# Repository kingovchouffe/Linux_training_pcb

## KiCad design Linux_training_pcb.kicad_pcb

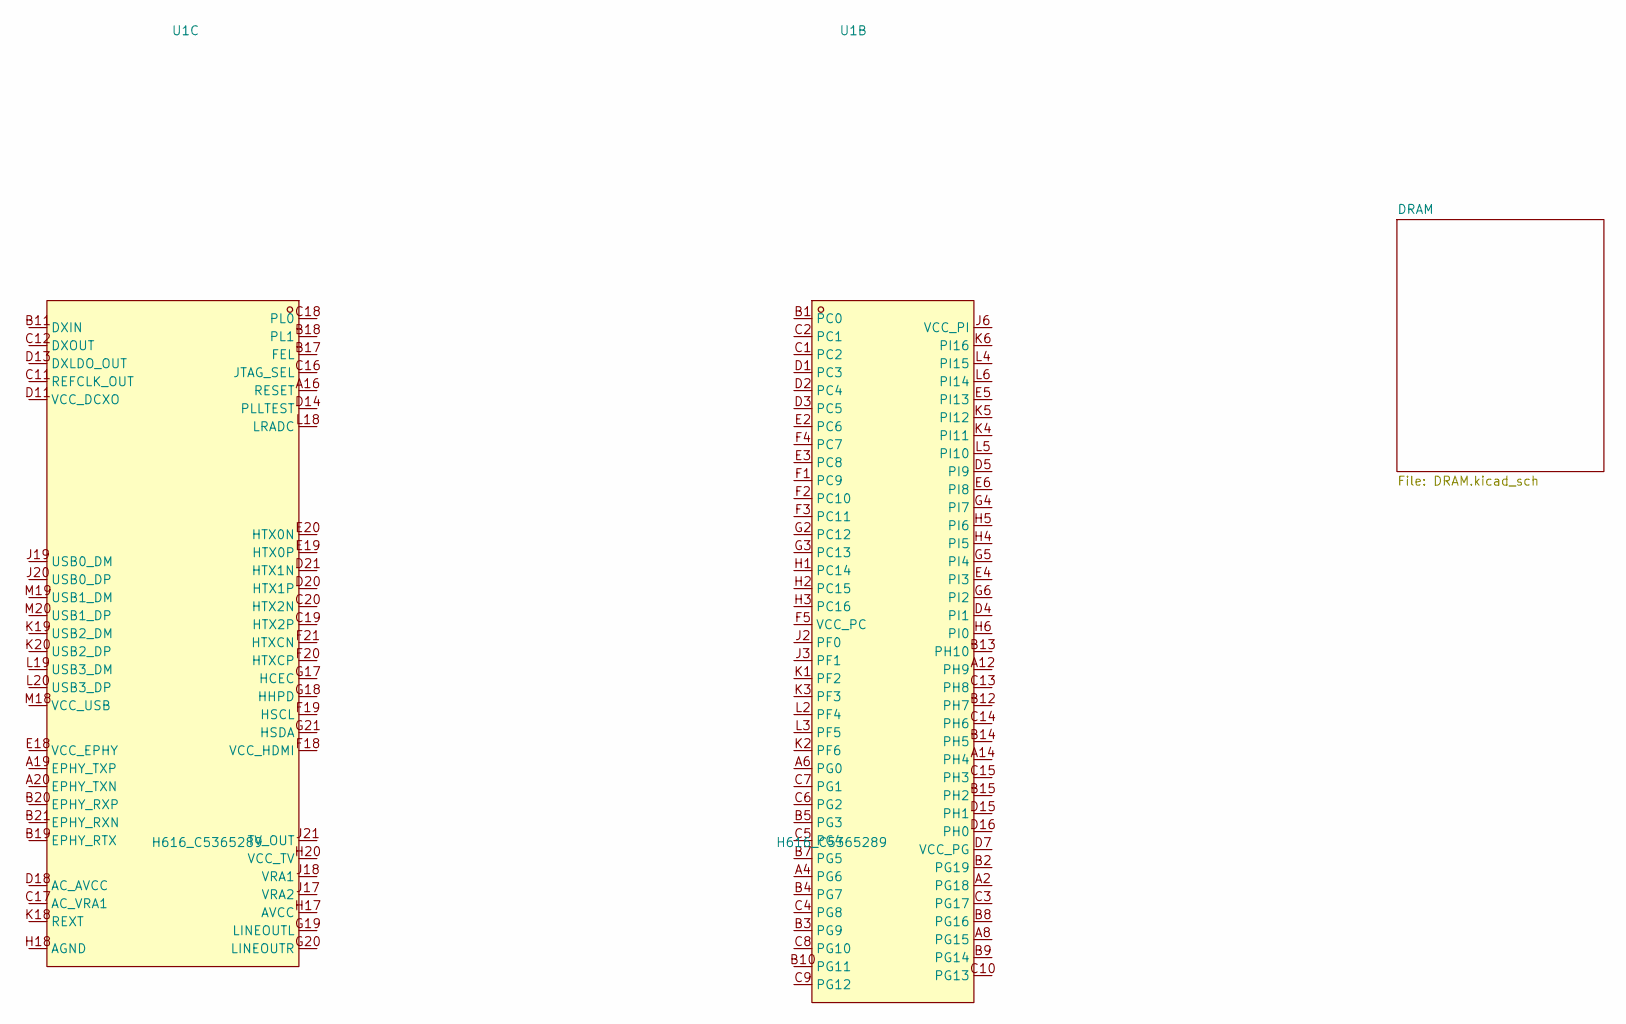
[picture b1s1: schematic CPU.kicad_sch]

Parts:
U1: H616_C5365289; BGA-284_L14.0-W12.0-P0.65-TL; MPN H616; LCSC Part C5365289

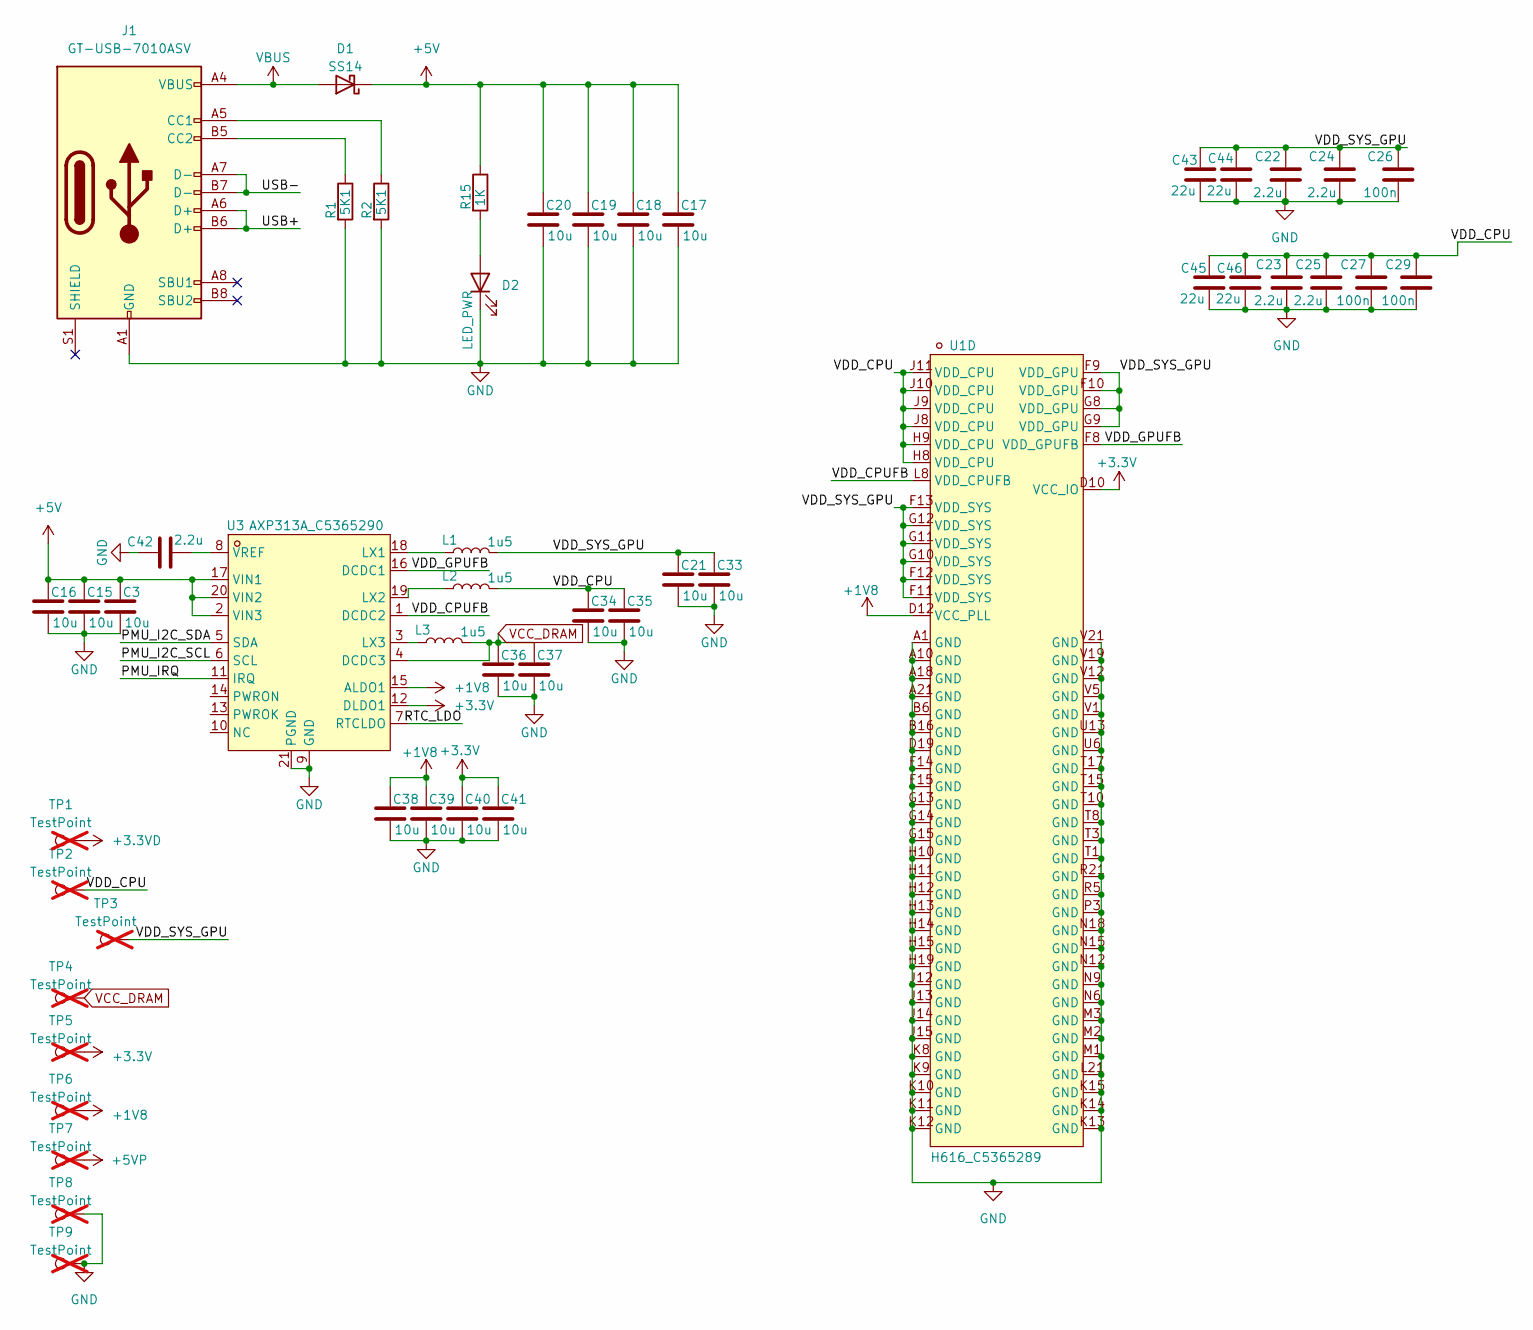
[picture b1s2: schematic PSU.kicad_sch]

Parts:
C3, C15, C16, C17, C18, C19, C20, C21, C33, C34, C35, C36, C37, C38, C39, C40, C41: 10u; C_0603_1608Metric
C22, C23, C24, C25, C42: 2.2u; C_0402_1005Metric; Part Number CL05A225KO5NQNC
C26, C27, C29: 100n; C_0402_1005Metric; Part Number CL05A225KO5NQNC
C43, C44, C45, C46: 22u; C_0603_1608Metric
D1: SS14; D_SMA
D2: LED_PWR; LED_0603_1608Metric
J1: GT-USB-7010ASV; USB_C_Receptacle_G-Switch_GT-USB-7010ASV
L1, L2, L3: 1u5; L_Changjiang_FNR252010S
R1, R2: 5K1; R_0603_1608Metric
R15: 1K; R_0603_1608Metric
TP1, TP2, TP3, TP4, TP5, TP6, TP7, TP8, TP9: TestPoint; TestPoint_Pad_D1.0mm; not fitted
U1: H616_C5365289; BGA-284_L14.0-W12.0-P0.65-TL; MPN H616; LCSC Part C5365289
U3: AXP313A_C5365290; QFN-20_L3.0-W3.0-P0.40-BL-EP1.7; MPN AXP313A; LCSC Part C5365290

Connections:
+1V8: C38.1, C39.1, TP6.1 (1_1), U1.D12 (VCC_PLL), U3.15 (ALDO1); also elsewhere on the board
+3.3V: C40.1, C41.1, TP5.1 (1_1), U1.D10 (VCC_IO), U3.12 (DLDO1)
+3.3VD: TP1.1 (1_1)
+5V: C3.1, C15.1, C16.1, C17.1, C18.1, C19.1, C20.1, D1.1 (K), R15.1, U3.2 (VIN3), U3.17 (VIN1), U3.20 (VIN2)
+5VP: TP7.1 (1_1)
/PSU/RTC_LDO: U3.7 (RTCLDO)
/PSU/USB+: J1.A6 (D+), J1.B6 (D+)
/PSU/USB-: J1.A7 (D-), J1.B7 (D-)
/PSU/VDD_CPU: C23.1, C25.1, C27.1, C29.1, C34.1, C35.1, C45.1, C46.1, L2.2, TP2.1 (1_1), U1.H8 (VDD_CPU), U1.H9 (VDD_CPU), U1.J8 (VDD_CPU), U1.J9 (VDD_CPU), U1.J10 (VDD_CPU), U1.J11 (VDD_CPU)
/PSU/VDD_CPUFB: U1.L8 (VDD_CPUFB), U3.1 (DCDC2)
/PSU/VDD_GPUFB: U1.F8 (VDD_GPUFB), U3.16 (DCDC1)
/PSU/VDD_SYS_GPU: C21.1, C22.1, C24.1, C26.1, C33.1, C43.1, C44.1, L1.2, TP3.1 (1_1), U1.F9 (VDD_GPU), U1.F10 (VDD_GPU), U1.F11 (VDD_SYS), U1.F12 (VDD_SYS), U1.F13 (VDD_SYS), U1.G8 (VDD_GPU), U1.G9 (VDD_GPU), U1.G10 (VDD_SYS), U1.G11 (VDD_SYS), U1.G12 (VDD_SYS)
GND: C3.2, C15.2, C16.2, C17.2, C18.2, C19.2, C20.2, C21.2, C22.2, C23.2, C24.2, C25.2, C26.2, C27.2, C29.2, C33.2, C34.2, C35.2, C36.2, C37.2, C38.2, C39.2, C40.2, C41.2, C42.2, C43.2, C44.2, C45.2, C46.2, D2.1 (K), J1.A1 (GND), J1.A12 (GND), J1.B1 (GND), J1.B12 (GND), R1.2, R2.2, TP8.1 (1_1), TP9.1 (1_1), U1.A1 (GND), U1.A10 (GND), U1.A18 (GND), U1.A21 (GND), U1.B6 (GND), U1.B16 (GND), U1.D19 (GND), U1.F14 (GND), U1.F15 (GND), U1.G13 (GND), U1.G14 (GND), U1.G15 (GND), U1.H10 (GND), U1.H11 (GND), U1.H12 (GND), U1.H13 (GND), U1.H14 (GND), U1.H15 (GND), U1.H19 (GND), U1.J12 (GND), U1.J13 (GND), U1.J14 (GND), U1.J15 (GND), U1.K8 (GND), U1.K9 (GND), U1.K10 (GND), U1.K11 (GND), U1.K12 (GND), U1.K13 (GND), U1.K14 (GND), U1.K15 (GND), U1.L21 (GND), U1.M1 (GND), U1.M2 (GND), U1.M3 (GND), U1.N6 (GND), U1.N9 (GND), U1.N12 (GND), U1.N15 (GND), U1.N18 (GND), U1.P3 (GND), U1.R5 (GND), U1.R21 (GND), U1.T1 (GND), U1.T3 (GND), U1.T8 (GND), U1.T10 (GND), U1.T15 (GND), U1.T17 (GND), U1.U6 (GND), U1.U13 (GND), U1.V1 (GND), U1.V5 (GND), U1.V12 (GND), U1.V19 (GND), U1.V21 (GND), U3.9 (GND), U3.21 (PGND); also elsewhere on the board
unnamed: D2.2 (A), R15.2
unnamed: J1.A5 (CC1), R2.1
unnamed: J1.B5 (CC2), R1.1
unnamed: L1.1, U3.18 (LX1)
unnamed: L2.1, U3.19 (LX2)
unnamed: L3.1, U3.3 (LX3)
unnamed: C42.1, U3.8 (VREF)
VBUS: D1.2 (A), J1.A4 (VBUS), J1.A9 (VBUS), J1.B4 (VBUS), J1.B9 (VBUS)
VCC_DRAM: C36.1, C37.1, L3.2, TP4.1 (1_1), U3.4 (DCDC3); also elsewhere on the board

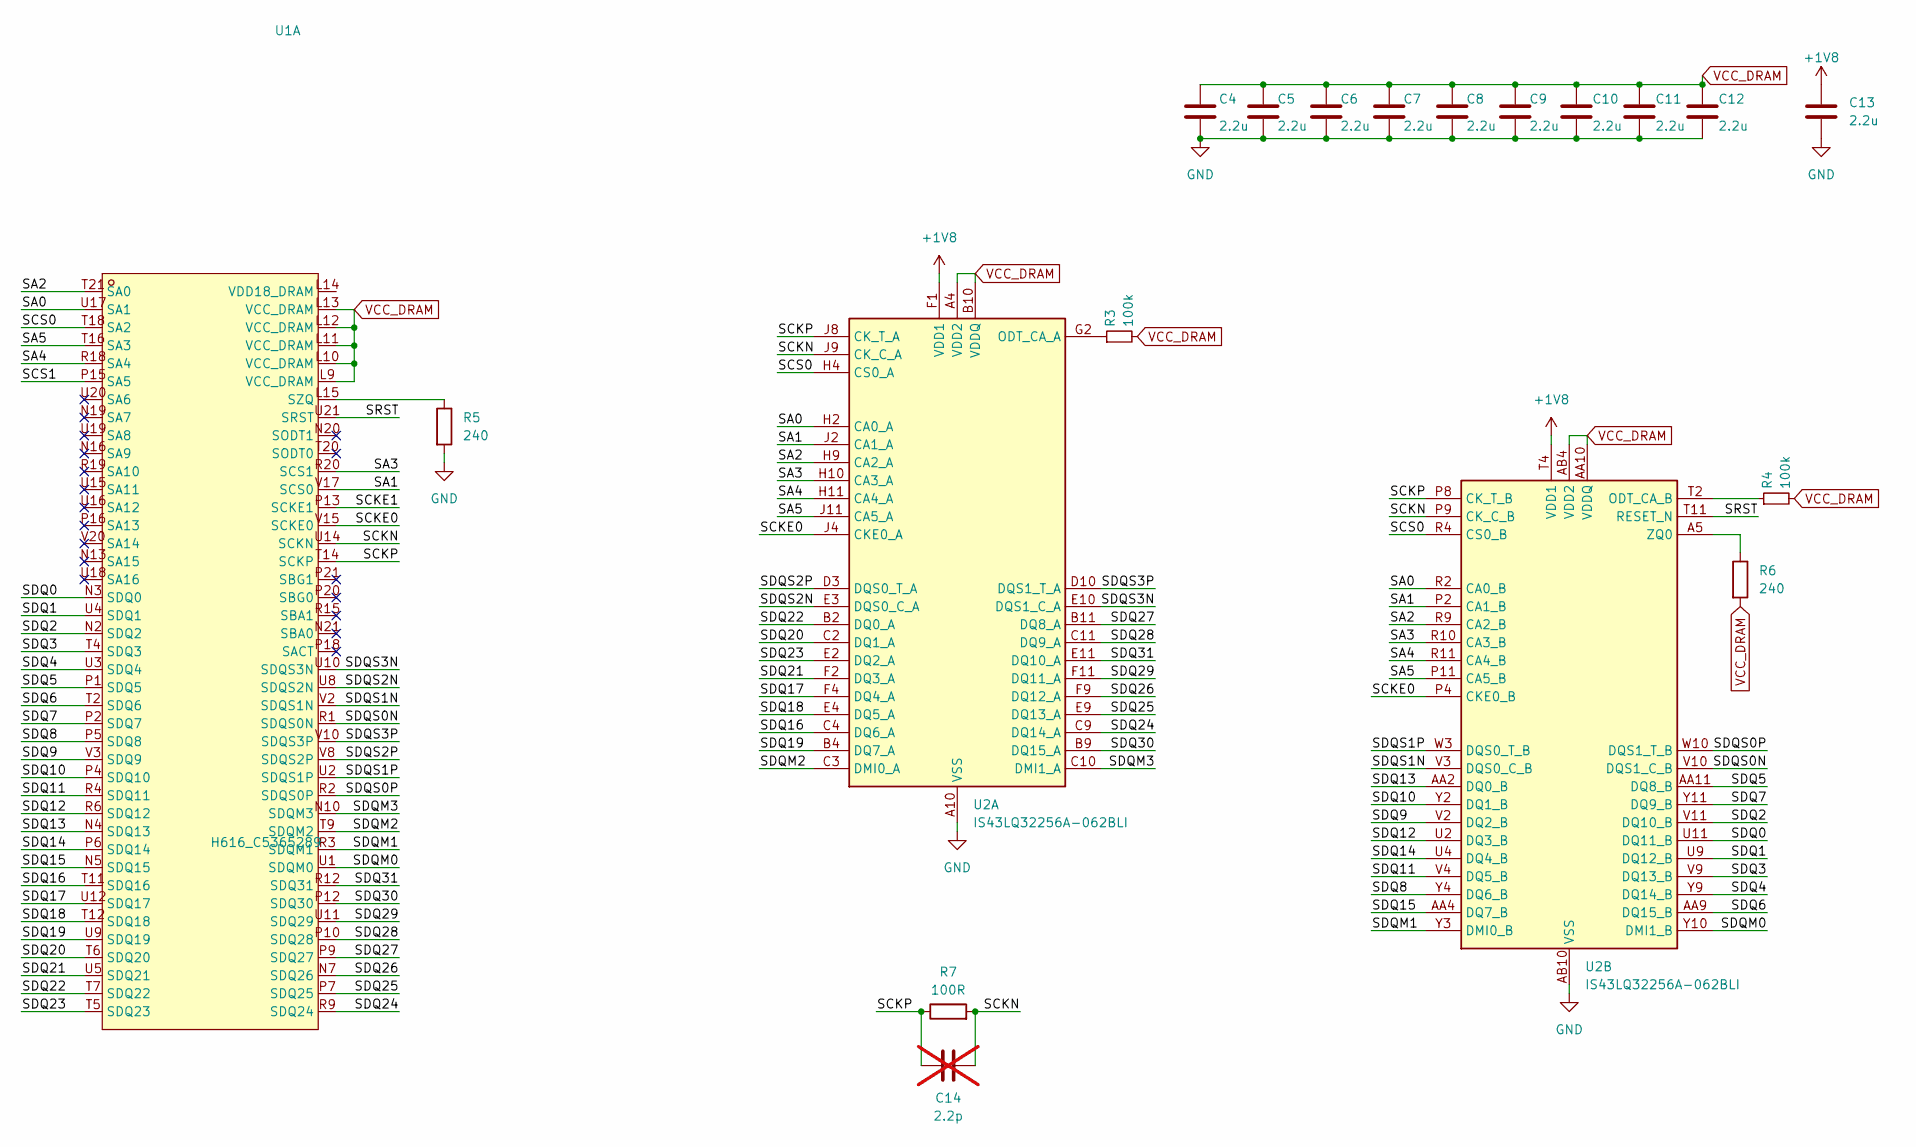
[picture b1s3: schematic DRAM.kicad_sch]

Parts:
C4, C5, C6, C7, C8, C9, C10, C11, C12, C13: 2.2u; C_0402_1005Metric; Part Number CL05A225KO5NQNC
C14: 2.2p; C_0402_1005Metric; not fitted
R3, R4: 100k; R_0603_1608Metric; Part Number RC0402FR-07100KL
R5, R6: 240; R_0603_1608Metric
R7: 100R; R_0603_1608Metric; Part Number RC0402FR-07100RL
U1: H616_C5365289; BGA-284_L14.0-W12.0-P0.65-TL; MPN H616; LCSC Part C5365289
U2: IS43LQ32256A-062BLI; BGA-200_10x14.5mm_Layout12x22_P0.8x0.65mm

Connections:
+1V8: C13.1, U2.F1 (VDD1), U2.F12 (VDD1), U2.G4 (VDD1), U2.G9 (VDD1), U2.T4 (VDD1), U2.T9 (VDD1), U2.U1 (VDD1), U2.U12 (VDD1); also elsewhere on the board
/CPU/DRAM/SA0: U1.U17 (SA1), U2.H2 (CA0_A), U2.R2 (CA0_B)
/CPU/DRAM/SA1: U1.V17 (SCS0), U2.J2 (CA1_A), U2.P2 (CA1_B)
/CPU/DRAM/SA2: U1.T21 (SA0), U2.H9 (CA2_A), U2.R9 (CA2_B)
/CPU/DRAM/SA3: U1.R20 (SCS1), U2.H10 (CA3_A), U2.R10 (CA3_B)
/CPU/DRAM/SA4: U1.R18 (SA4), U2.H11 (CA4_A), U2.R11 (CA4_B)
/CPU/DRAM/SA5: U1.T16 (SA3), U2.J11 (CA5_A), U2.P11 (CA5_B)
/CPU/DRAM/SCKE0: U1.V15 (SCKE0), U2.J4 (CKE0_A), U2.P4 (CKE0_B)
/CPU/DRAM/SCKE1: U1.P13 (SCKE1)
/CPU/DRAM/SCKN: C14.2, R7.2, U1.U14 (SCKN), U2.J9 (CK_C_A), U2.P9 (CK_C_B)
/CPU/DRAM/SCKP: C14.1, R7.1, U1.T14 (SCKP), U2.J8 (CK_T_A), U2.P8 (CK_T_B)
/CPU/DRAM/SCS0: U1.T18 (SA2), U2.H4 (CS0_A), U2.R4 (CS0_B)
/CPU/DRAM/SCS1: U1.P15 (SA5)
/CPU/DRAM/SDQ0: U1.N3 (SDQ0), U2.U11 (DQ11_B)
/CPU/DRAM/SDQ1: U1.U4 (SDQ1), U2.U9 (DQ12_B)
/CPU/DRAM/SDQ2: U1.N2 (SDQ2), U2.V11 (DQ10_B)
/CPU/DRAM/SDQ3: U1.T4 (SDQ3), U2.V9 (DQ13_B)
/CPU/DRAM/SDQ4: U1.U3 (SDQ4), U2.Y9 (DQ14_B)
/CPU/DRAM/SDQ5: U1.P1 (SDQ5), U2.AA11 (DQ8_B)
/CPU/DRAM/SDQ6: U1.T2 (SDQ6), U2.AA9 (DQ15_B)
/CPU/DRAM/SDQ7: U1.P2 (SDQ7), U2.Y11 (DQ9_B)
/CPU/DRAM/SDQ8: U1.P5 (SDQ8), U2.Y4 (DQ6_B)
/CPU/DRAM/SDQ9: U1.V3 (SDQ9), U2.V2 (DQ2_B)
/CPU/DRAM/SDQ10: U1.P4 (SDQ10), U2.Y2 (DQ1_B)
/CPU/DRAM/SDQ11: U1.R4 (SDQ11), U2.V4 (DQ5_B)
/CPU/DRAM/SDQ12: U1.R6 (SDQ12), U2.U2 (DQ3_B)
/CPU/DRAM/SDQ13: U1.N4 (SDQ13), U2.AA2 (DQ0_B)
/CPU/DRAM/SDQ14: U1.P6 (SDQ14), U2.U4 (DQ4_B)
/CPU/DRAM/SDQ15: U1.N5 (SDQ15), U2.AA4 (DQ7_B)
/CPU/DRAM/SDQ16: U1.T11 (SDQ16), U2.C4 (DQ6_A)
/CPU/DRAM/SDQ17: U1.U12 (SDQ17), U2.F4 (DQ4_A)
/CPU/DRAM/SDQ18: U1.T12 (SDQ18), U2.E4 (DQ5_A)
/CPU/DRAM/SDQ19: U1.U9 (SDQ19), U2.B4 (DQ7_A)
/CPU/DRAM/SDQ20: U1.T6 (SDQ20), U2.C2 (DQ1_A)
/CPU/DRAM/SDQ21: U1.U5 (SDQ21), U2.F2 (DQ3_A)
/CPU/DRAM/SDQ22: U1.T7 (SDQ22), U2.B2 (DQ0_A)
/CPU/DRAM/SDQ23: U1.T5 (SDQ23), U2.E2 (DQ2_A)
/CPU/DRAM/SDQ24: U1.R9 (SDQ24), U2.C9 (DQ14_A)
/CPU/DRAM/SDQ25: U1.P7 (SDQ25), U2.E9 (DQ13_A)
/CPU/DRAM/SDQ26: U1.N7 (SDQ26), U2.F9 (DQ12_A)
/CPU/DRAM/SDQ27: U1.P9 (SDQ27), U2.B11 (DQ8_A)
/CPU/DRAM/SDQ28: U1.P10 (SDQ28), U2.C11 (DQ9_A)
/CPU/DRAM/SDQ29: U1.U11 (SDQ29), U2.F11 (DQ11_A)
/CPU/DRAM/SDQ30: U1.P12 (SDQ30), U2.B9 (DQ15_A)
/CPU/DRAM/SDQ31: U1.R12 (SDQ31), U2.E11 (DQ10_A)
/CPU/DRAM/SDQM0: U1.U1 (SDQM0), U2.Y10 (DMI1_B)
/CPU/DRAM/SDQM1: U1.R3 (SDQM1), U2.Y3 (DMI0_B)
/CPU/DRAM/SDQM2: U1.T9 (SDQM2), U2.C3 (DMI0_A)
/CPU/DRAM/SDQM3: U1.N10 (SDQM3), U2.C10 (DMI1_A)
/CPU/DRAM/SDQS0N: U1.R1 (SDQS0N), U2.V10 (DQS1_C_B)
/CPU/DRAM/SDQS0P: U1.R2 (SDQS0P), U2.W10 (DQS1_T_B)
/CPU/DRAM/SDQS1N: U1.V2 (SDQS1N), U2.V3 (DQS0_C_B)
/CPU/DRAM/SDQS1P: U1.U2 (SDQS1P), U2.W3 (DQS0_T_B)
/CPU/DRAM/SDQS2N: U1.U8 (SDQS2N), U2.E3 (DQS0_C_A)
/CPU/DRAM/SDQS2P: U1.V8 (SDQS2P), U2.D3 (DQS0_T_A)
/CPU/DRAM/SDQS3N: U1.U10 (SDQS3N), U2.E10 (DQS1_C_A)
/CPU/DRAM/SDQS3P: U1.V10 (SDQS3P), U2.D10 (DQS1_T_A)
/CPU/DRAM/SRST: U1.U21 (SRST), U2.T11 (RESET_N)
GND: C4.2, C5.2, C6.2, C7.2, C8.2, C9.2, C10.2, C11.2, C12.2, C13.2, R5.2, U2.A3 (VSS), U2.A10 (VSS), U2.AB3 (VSS), U2.AB5 (VSS), U2.AB8 (VSS), U2.AB10 (VSS), U2.C1 (VSS), U2.C5 (VSS), U2.C8 (VSS), U2.C12 (VSS), U2.D2 (VSS), U2.D4 (VSS), U2.D9 (VSS), U2.D11 (VSS), U2.E1 (VSS), U2.E5 (VSS), U2.E8 (VSS), U2.E12 (VSS), U2.G1 (VSS), U2.G3 (VSS), U2.G5 (VSS), U2.G8 (VSS), U2.G10 (VSS), U2.G12 (VSS), U2.J1 (VSS), U2.J3 (VSS), U2.J10 (VSS), U2.J12 (VSS), U2.K2 (VSS), U2.K4 (VSS), U2.K9 (VSS), U2.K11 (VSS), U2.N2 (VSS), U2.N4 (VSS), U2.N9 (VSS), U2.N11 (VSS), U2.P1 (VSS), U2.P3 (VSS), U2.P10 (VSS), U2.P12 (VSS), U2.T1 (VSS), U2.T3 (VSS), U2.T5 (VSS), U2.T8 (VSS), U2.T10 (VSS), U2.T12 (VSS), U2.V1 (VSS), U2.V5 (VSS), U2.V8 (VSS), U2.V12 (VSS), U2.W2 (VSS), U2.W4 (VSS), U2.W9 (VSS), U2.W11 (VSS), U2.Y1 (VSS), U2.Y5 (VSS), U2.Y8 (VSS), U2.Y12 (VSS); also elsewhere on the board
unnamed: R5.1, U1.L15 (SZQ)
unnamed: R3.1, U2.G2 (ODT_CA_A)
unnamed: R4.1, U2.T2 (ODT_CA_B)
unnamed: R6.1, U2.A5 (ZQ0)
VCC_DRAM: C4.1, C5.1, C6.1, C7.1, C8.1, C9.1, C10.1, C11.1, C12.1, R3.2, R4.2, R6.2, U1.L9 (VCC_DRAM), U1.L10 (VCC_DRAM), U1.L11 (VCC_DRAM), U1.L12 (VCC_DRAM), U1.L13 (VCC_DRAM), U2.A4 (VDD2), U2.A9 (VDD2), U2.AA3 (VDDQ), U2.AA5 (VDDQ), U2.AA8 (VDDQ), U2.AA10 (VDDQ), U2.AB4 (VDD2), U2.AB9 (VDD2), U2.B3 (VDDQ), U2.B5 (VDDQ), U2.B8 (VDDQ), U2.B10 (VDDQ), U2.D1 (VDDQ), U2.D5 (VDDQ), U2.D8 (VDDQ), U2.D12 (VDDQ), U2.F3 (VDDQ), U2.F5 (VDD2), U2.F8 (VDD2), U2.F10 (VDDQ), U2.H1 (VDD2), U2.H5 (VDD2), U2.H8 (VDD2), U2.H12 (VDD2), U2.K1 (VDD2), U2.K3 (VDD2), U2.K10 (VDD2), U2.K12 (VDD2), U2.N1 (VDD2), U2.N3 (VDD2), U2.N10 (VDD2), U2.N12 (VDD2), U2.R1 (VDD2), U2.R5 (VDD2), U2.R8 (VDD2), U2.R12 (VDD2), U2.U3 (VDDQ), U2.U5 (VDD2), U2.U8 (VDD2), U2.U10 (VDDQ), U2.W1 (VDDQ), U2.W5 (VDDQ), U2.W8 (VDDQ), U2.W12 (VDDQ); also elsewhere on the board

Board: 6 copper layers, 66 parts (13 on the bottom side), 78 nets, no tracks yet.
